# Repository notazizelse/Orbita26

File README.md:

# SnailPulse — Orbita 2026

**Measuring a living snail's heartbeat in the stratosphere.**
International Space Tournament *Orbita* 2026 · 3U CubeSat on the IntroSat.Platform · Team mentor: Ezoza Yuldosheva · Electronics and firmware: Azizbek No'monjonov

We fly two garden snails (*Cornu aspersum*) to about 24 km. Each has an infrared sensor glued to its shell that watches the heart beat through the shell. **Snail 1** has a TCRT5000 whose tiny signal goes through our analog band-pass amplifier into PB0. **Snail 2** has a MAX30100 optical pulse sensor read over I²C. The satellite's flight controller counts both hearts' beats and radios them to the ground every 2 seconds. Meanwhile a heater keeps the snail's box at 20 °C, and a hardware cutoff protects it even if the software fails.

*Concept render of the payload board. The flight unit is built on perfboard from the same schematic. [3D preview →](#3d-preview)*

## Schematic

*Rev B schematic, plotted from `hardware/kicad/Orbita26.kicad_sch` on 24 Oct 2026. Vector version for zooming and printing: [hardware/Orbita26_schematic.pdf](hardware/Orbita26_schematic.pdf). Block close-ups are under [How it works](#how-it-works).*

## What's new (24 Oct 2026)

- **Schematic picture redrawn.** `docs/images/schematic_full.png` and the five block close-ups now show rev B (`HEATER_LO`, J3 switched by Q1, NTC2 on J4.3). The old pictures were still from before the fixes. A vector PDF of the sheet is in `hardware/`.
- **Tournament final paperwork** added for the trip to Moscow (see [Orbita 2026 final](#orbita-2026-final-moscow)).
- **Parts list** added in two more forms: `SnailPulse_BOM.xlsx` at the top level (same file as `hardware/SnailPulse_BOM.xlsx`) and `Orbita SnailPulse Parts List.numbers` (the Numbers version with shop names and links).
- **Radio reference photo**: `micoair_lr900_915mhz_500mw_radio_telemetry_with_30km_range_5_550x550.jpeg`, the MicoAir LR900 telemetry radio pair (915 MHz, 500 mW).

## What's new (23 Oct 2026, schematic rev B)

The schematic in `hardware/kicad/Orbita26.kicad_sch` was re-checked today by extracting its netlist and comparing it pin by pin with the intended design.

**Result: all 21 nets connect exactly as designed.** The three rev A wiring errors are gone, and the only unconnected pin is the intentional no-connect on U5 pin 7.

| Change since rev A | Status |
|---|---|
| J3 heater cable now switched by Q1 (`HEATER_LO` on J3.2 and the Q1 drain) instead of sitting across the battery | ✅ fixed |
| J1 sensor cable connected to the circuit (`LED_A`, `SENSE` labels on both ends) | ✅ fixed |
| J4 pin 3 connected to the cutoff thermistor node (`NTC2` on R18 / TH2 / C7 / U5.3) | ✅ fixed |
| `HEATER_L0` (zero) renamed `HEATER_LO` | ✅ fixed |
| PWR_FLAG on every power net, including GNDPWR | ✅ added |
| Footprints on every on-board part (JST-XH, XT30, 5.0 mm screw terminal for the heater, DIP-8 sockets, THT R/C/trimmers, net tie) | ✅ added |
| U1 (TCRT5000), TH1, TH2, R8–R10 marked "exclude from board" (they live on cables) | ✅ done |
| Title block still says **rev A, 22 Oct** | ⬜ change to rev B |
| Reference gaps: R2, R4, R5, R14, C1, RV1, U3, U4 are unused | ⬜ run *Annotate* before exporting the BOM |

New documents:

- **[docs/Firmware_and_Integration.md](docs/Firmware_and_Integration.md)** explains how the flight code works (sampling, beat detection, heater control, packets, SD log, fault handling) and how SnailPulse plugs into the IntroSat flight controller, power module and radio board.
- **[docs/3d/](docs/3d/)** has the 3D preview of how the board could look as a PCB.

## How it works

| Block | What it does | Key numbers |
|---|---|---|
| **A. Heartbeat sensor + amplifier** | TCRT5000 IR reflectance through the shell → RV3 load → high-pass → ×101 amplifier with low-pass → PB0 | LED 17 mA · pass band 0.16–3.4 Hz (10–200 bpm) · gain 101 (40 dB) |
| **B. 1.65 V reference** | Divider + MCP6002 buffer; centres the signal in the 0–3.3 V ADC range | 3.3 V / 2, filtered at 3.2 Hz |
| **C1. Heater switch** | 3 × 150 Ω heater, IRLZ44N low-side switch, PWM from PC6 | 50 Ω · 0.30 A · 4.4 W at 14.8 V |
| **C2. Thermistors + hardware cutoff** | NTC1 → PB1 for firmware control; NTC2 → LM393 cuts the heater at ~40 °C with no software | 40 °C ↔ 1.14 V · −30 mV/°C |
| **D. Connectors** | Locking JST-XH plugs to the sensor, thermistors, flight controller, BMP280 and MAX30100 | I²C4 = PD12/PD13 · power from IntroBus_L and X8 |

Full sheet: [Schematic](#schematic) above.

<details><summary>Block close-ups (rev B)</summary>

</details>

Rev A review and the reasoning behind every block: [docs/Schematic_Review.md](docs/Schematic_Review.md).

## How it connects to the IntroSat.Platform

SnailPulse doesn't replace any platform board. It adds one payload board and our firmware on the existing flight controller (STM32H750).

| Our plug | Goes to | Signals |
|---|---|---|
| **J6** (5-pin) | IntroBus_L | PB0 heartbeat ADC · PB1 MQ-7 AO via 10k/20k divider (rev B: heater thermistor) · PC6 DHT-11 data (rev B: heater PWM) · DHT-11 and MQ-7 on +5 V · PD12/PD13 I²C4 |
| **J5** (3-pin) | IntroBus_L | +5V_IS · +3V3_IS · GND |
| **J2** (XT30) | Power module X8 | 14.8 V for the heater only (red +, black −) |
| **J7 / J8 / J9** | (empty: GY-21 removed 30 Oct) · BMP280 · MAX30100 (snail 2's pulse sensor) | I²C4 at — · 0x76 · 0x57 |

Data path: PB0 (snail 1) is sampled at 50 Hz in a timer interrupt and the MAX30100 (snail 2) is read at 100 Hz over I²C4 → one beat detector per snail → binary packet → UART1 → communication board → LoRa 433 MHz → ground LoRa-UART module → `ground/snailpulse_ground.py`. The full story, with the pin table, power budget and failure handling, is in [docs/Firmware_and_Integration.md](docs/Firmware_and_Integration.md).

## 3D preview

| | |
|---|---|
|  |  |
|  |  |

- `docs/3d/SnailPulse_3D.html`: interactive viewer. Download it and open it in a browser (needs internet for the 3D library). Turn the board, look underneath, click any part to see its job and its nets.
- `docs/3d/SnailPulse_board.glb`: the same model as a 3D file, in metres. Opens in Blender, the Windows 3D Viewer, or any online glTF viewer.

Reference numbers in the preview match the schematic. It is a **concept render, not a fabrication file**: the parts and footprints are real, but the board outline, positions and the traces painted on its surface are illustrative.

## Orbita 2026 final (Moscow)

The final runs from **26 October to 1 November 2026** at Bauman Moscow State Technical University, organized by ANO CIKENO together with HSE University. Arrival and workstation setup are on 25 October.

| File | What it is |
|---|---|
| `International_tournament_Orbita_Schedule_EN.pdf` | Day-by-day programme of the final (venues, lab hours, excursions) |
| `Письмо ЦИКЕНО Узбекистан.pdf` | Organizers' letter No. 22-10-26/3 (22 Oct 2026) confirming the Uzbek delegation as finalists |
| `russia team.pdf` | Uzbekistan delegation list with each member's role (in Uzbek) |
| `ClearView — presentation (EN).pdf` | Our delegation's Cosmonautics Project Contest entry: *ClearView*, a spacesuit visor wiper with a self-cleaning edge (13 slides) |

## Repository

**Start here:** [HANDOFF.md](HANDOFF.md) (where the work stands and what's next) · [docs/Software_Setup.md](docs/Software_Setup.md) (build, flash and debug on macOS/Windows, also from Russia; Mac: `bash scripts/mac_setup.sh`) · [docs/Bench_Test.md](docs/Bench_Test.md) (what plugs where, power order, upload, ground monitor) · [radio_handoff/](radio_handoff/README.md) (for the radio technician) · [CLAUDE.md](CLAUDE.md) (project rules, pins, build and test commands) · [hardware/perfboard/SnailPulse_perfboard_build.html](hardware/perfboard/SnailPulse_perfboard_build.html) (build guide).

```
Orbita26/
├── README.md                     ← you are here
├── HANDOFF.md                    current state + next steps
├── CLAUDE.md                     rules, pins, build/test commands
├── firmware/build_backup/        E32 LoRa config script, rev C heater patch (history)
├── International_tournament_Orbita_Schedule_EN.pdf   final programme      (new)
├── Письмо ЦИКЕНО Узбекистан.pdf  organizers' confirmation letter          (new)
├── russia team.pdf               delegation list                         (new)
├── ClearView — presentation (EN).pdf   Cosmonautics Project Contest entry (new)
├── SnailPulse_BOM.xlsx           copy of hardware/SnailPulse_BOM.xlsx     (new)
├── Orbita SnailPulse Parts List.numbers   parts list with shop links     (new)
├── SnailPulse_KiCad_Connections.numbers   wiring workbook (Numbers)
├── micoair_lr900_…_550x550.jpeg  MicoAir LR900 radio photo                (new)
├── hardware/
│   ├── kicad/                    KiCad 10 project (Orbita26.kicad_pro / .kicad_sch)
│   ├── Orbita26_schematic.pdf    rev B schematic, vector                  (new)
│   ├── SnailPulse_BOM.xlsx       parts + prices (Microelectronica, electron.uz)
│   ├── SnailPulse_KiCad_Connections.xlsx   pin-by-pin wiring workbook
│   ├── SnailPulse_wiring.pdf
│   └── SnailPulse_shopping_list.md
├── firmware/                     flight code for the IntroSat flight controller → firmware/README.md
├── ground/snailpulse_monitor.py  live ground screen: every sensor with OK/WARN/FAIL (browser)
├── ground/snailpulse_ground.py   ground-station decoder (serial → console + CSV + plots)
├── radio_handoff/                frame format, C header, examples for the radio technician
├── scripts/mac_setup.sh          one-shot Mac setup (Arduino IDE fix, toolchain, monitor)
├── docs/
│   ├── Firmware_and_Integration.md  how the code works and plugs into IntroSat   (new)
│   ├── 3d/                       3D preview: viewer, .glb model, renders          (new)
│   ├── SnailPulse_Study_Guide.md every part explained + jury Q&A in Russian
│   ├── SnailPulse_Math.md        every formula and number
│   ├── Schematic_Review.md       rev A review and fixes
│   ├── images/                   schematic renders (rev B, redrawn 24 Oct)
│   └── research/                 mission and camera-payload research notes
├── resources/                    organizer documents (IntroSat guide EN/RU, missions, Orbita 2025)
└── budget/smeta.numbers          cost estimate
```

## Telemetry

The flight controller sends four binary packet types. Each fits in one 58-byte LoRa packet and is protected by a CRC-16.

| Packet | Every | Contents |
|---|---|---|
| SNAIL | 2 s | snail 1 (TCRT5000): heart rate, last beat interval, beat count, signal quality, 2 s of waveform at 10 Hz · snail 2 (MAX30100): heart rate, beat count, quality, IR level |
| BASE | 2 s | flight-controller sensors: pressure, ISA altitude, accel, gyro, magnetometer, board temperature |
| ENV | 4 s | box temperature and pressure (BMP280), DHT-11 temperature/humidity, MQ-7 gas level, sensor status |
| STATUS | 10 s | firmware version, boot count, radio and I²C/SD error counters, watchdog resets |

Total is about 435 bit/s, 18 % of the 2.4 kbit/s link. Everything is also logged to microSD at full rate.

Ground station: `python3 ground/snailpulse_monitor.py --port <port> --baud <rate>` (live screen; `--demo` without hardware) or `python ground/snailpulse_ground.py --port <LoRa-UART port> --baud <its UART rate>` (console + CSV). After the flight: `snailpulse_ground.py --plot logs/`.

## Still to do before flight

- [ ] Title block → rev B; run *Annotate* to close the reference gaps.
- [ ] First compile and run of `SnailPulse_Flight` on the real flight controller (it passes the PC tests and a syntax check, but hasn't run on the STM32 yet).
- [ ] Tune RV3 on a live snail with `firmware/tools/HB_Tune`; set RV2 to ≈ 1.1 V and test the 40 °C cutoff.
- [ ] Freezer run of the whole stack for ~3 hours.

## Bill of materials (main parts)

TCRT5000 · MCP6002 · LM393 · IRLZ44N · 3 × 150 Ω 5 W · 2 × NTC 10 k · trimmers 50 k and 10 k · BMP280 · MAX30100 · JST-XH connectors · XT30. The full list with prices is in `hardware/SnailPulse_BOM.xlsx` (≈ 403 000 UZS including spares).

## Credits

Built on the organizers' IntroSat.Platform and [IntroStratLib](https://github.com/Obu-IntroSat/IntroStratLib-Public). The heartbeat method follows the IR-through-shell technique of Depledge & Andersen (1990) and Burnett et al. (2013). See the study guide for all sources.

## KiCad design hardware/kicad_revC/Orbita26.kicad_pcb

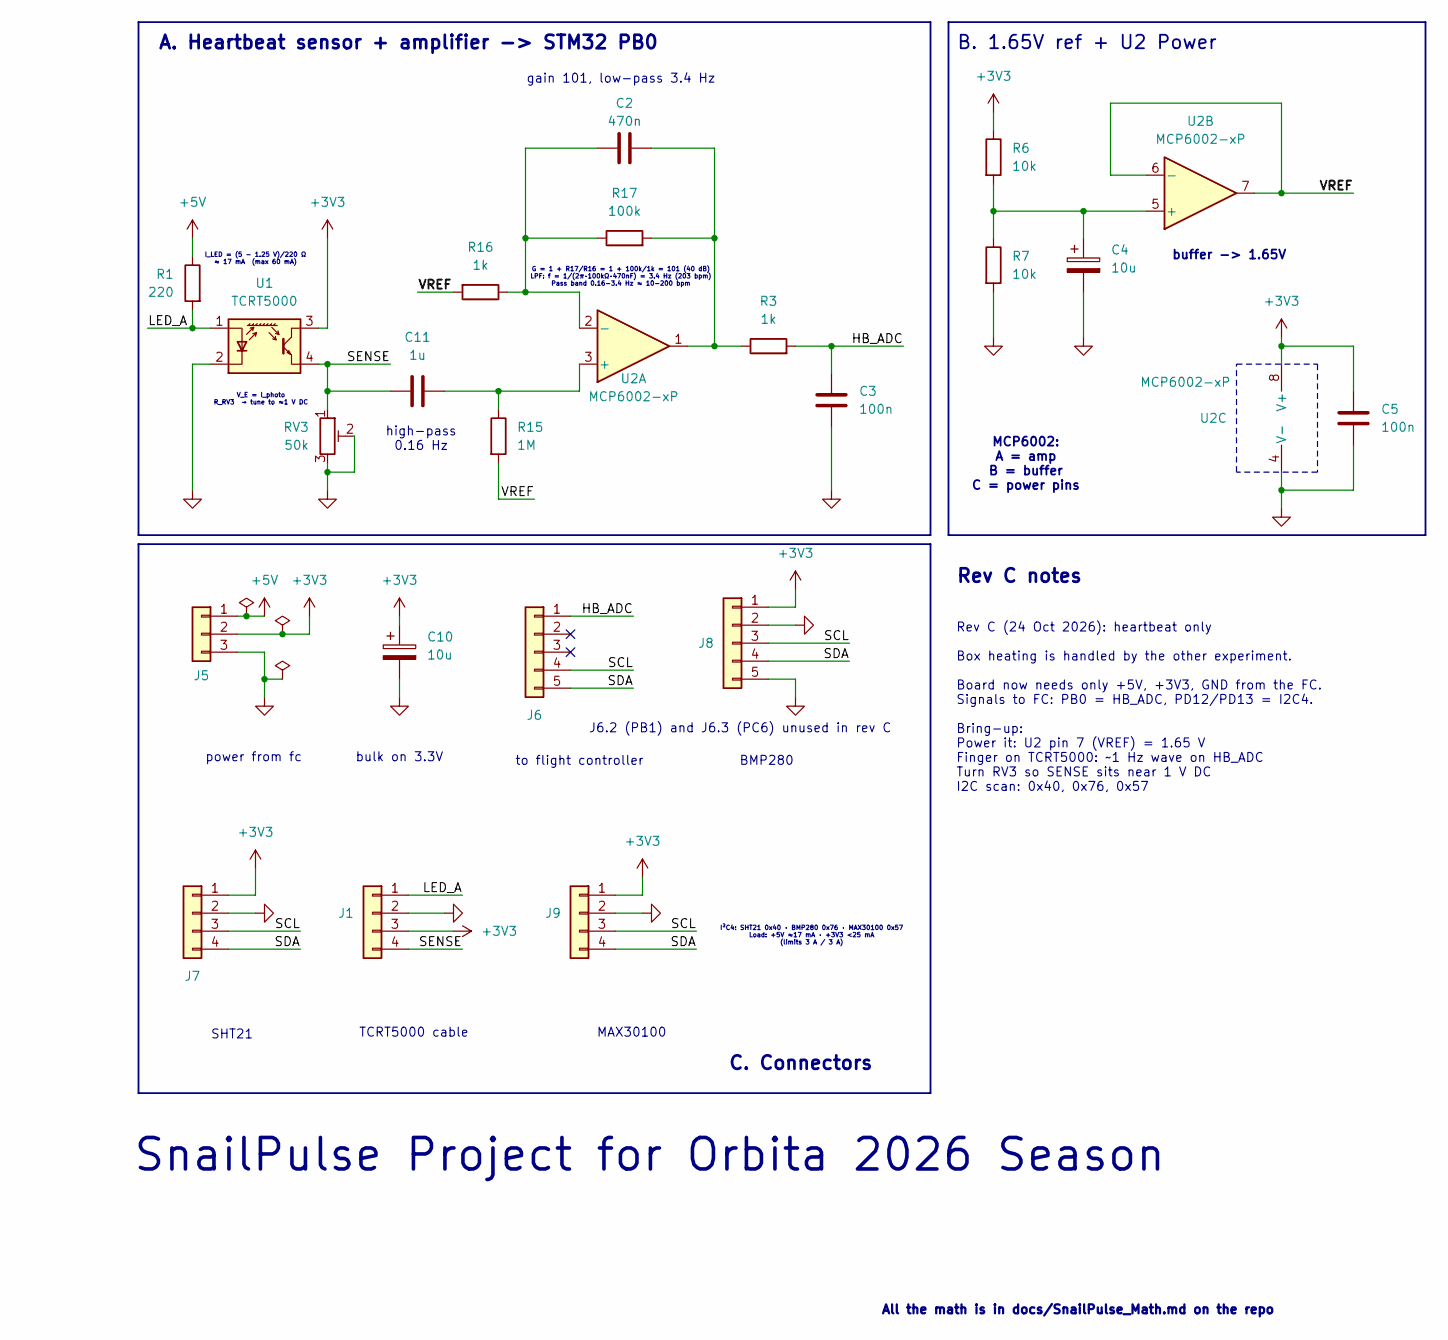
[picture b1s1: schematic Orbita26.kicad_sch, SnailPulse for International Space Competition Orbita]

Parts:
C2: 470n; C_Disc_D5.0mm_W2.5mm_P5.00mm
C3, C5: 100n; C_Disc_D5.0mm_W2.5mm_P5.00mm
C4, C10: 10u; CP_Radial_D5.0mm_P2.00mm
C11: 1u; C_Disc_D5.0mm_W2.5mm_P5.00mm
J1: Conn_1x4; JST_XH_B4B-XH-A_1x04_P2.50mm_Vertical
J5: Conn_01x03; JST_XH_B3B-XH-A_1x03_P2.50mm_Vertical
J6, J8: Conn_01x05; JST_XH_B5B-XH-A_1x05_P2.50mm_Vertical
J7, J9: Conn_01x04; JST_XH_B4B-XH-A_1x04_P2.50mm_Vertical
R1: 220; R_Axial_DIN0207_L6.3mm_D2.5mm_P7.62mm_Horizontal
R3, R16: 1k; R_Axial_DIN0207_L6.3mm_D2.5mm_P7.62mm_Horizontal
R6, R7: 10k; R_Axial_DIN0207_L6.3mm_D2.5mm_P7.62mm_Horizontal
R15: 1M; R_Axial_DIN0207_L6.3mm_D2.5mm_P7.62mm_Horizontal
R17: 100k; R_Axial_DIN0207_L6.3mm_D2.5mm_P7.62mm_Horizontal
RV3: 50k; Potentiometer_Bourns_3296W_Vertical
U1: TCRT5000; Vishay_CNY70
U2: MCP6002-xP; DIP-8_W7.62mm_Socket

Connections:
+3V3: C5.1, C10.1, J1.3, J5.2, J7.1, J8.1, J9.1, R6.1, U1.3 (C), U2.8 (V+)
+5V: J5.1, R1.1
/HB_ADC: C3.1, J6.1, R3.2
/LED_A: J1.1, R1.2, U1.1 (A)
/SCL: J6.4, J7.3, J8.3, J9.3
/SDA: J6.5, J7.4, J8.4, J9.4
/SENSE: C11.1, J1.4, RV3.1, U1.4 (E)
/VREF: R15.2, R16.2, U2.6 (-), U2.7
GND: C3.2, C4.2, C5.2, C10.2, J1.2, J5.3, J7.2, J8.2, J8.5, J9.2, R7.2, RV3.2, RV3.3, U1.2 (K), U2.4 (V-)
unnamed: C2.2, R3.1, R17.2, U2.1
unnamed: C11.2, R15.1, U2.3 (+)
unnamed: C2.1, R16.1, R17.1, U2.2 (-)
unnamed: C4.1, R6.2, R7.1, U2.5 (+)

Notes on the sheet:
power from fc
Rev C (24 Oct 2026): heartbeat only Box heating is handled by the other experiment. Board now needs only +5V, +3V3, GND from the FC. Signals to FC: PB0 = HB_ADC, PD12/PD13 = I2C4. Bring-up: Power it: U2 pin 7 (VREF) = 1.65 V Finger on TCRT5000: ~1 Hz wave on HB_ADC Turn RV3 so SENSE sits near 1 V D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
BMP280
buffer -> 1.65V
I²C4: SHT21 0x40 · BMP280 0x76 · MAX30100 0x57 Load: +5V ≈17 mA · +3V3 <25 mA (limits 3 A / 3 A)
to flight controller
MAX30100
SnailPulse Project for Orbita 2026 Season
SHT21
V_E = I_photo R_RV3 → tune to ≈1 V DC
J6.2 (PB1) and J6.3 (PC6) unused in rev C
bulk on 3.3V
I_LED = (5 − 1.25 V)/220 Ω ≈ 17 mA (max 60 mA)
G = 1 + R17/R16 = 1 + 100k/1k = 101 (40 dB) LPF: f = 1/(2π·100kΩ·470nF) = 3.4 Hz (203 bpm) Pass band 0.16-3.4 Hz ≈ 10-200 bpm
C. Connectors
B. 1.65V ref + U2 Power
TCRT5000 cable
gain 101, low-pass 3.4 Hz
A. Heartbeat sensor + amplifier -> STM32 PB0
high-pass 0.16 Hz
All the math is in docs/SnailPulse_Math.md on the repo
MCP6002: A = amp B = buffer C = power pins
Rev C notes

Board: 2 copper layers, 21 parts (0 on the bottom side), 13 nets, no tracks yet.
